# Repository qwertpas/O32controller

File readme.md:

Small robots often use servos or small brushed DC motors, but they are not as power dense as the brushless DC (BLDC) motors commonly found in drones. Called the Ø32 because the M2 mounting holes are on a 32mm diameter circle, this project controls 7-15V motors with accurate position feedback and field-oriented control (FOC), while fitting almost completely behind a 2304 or larger drone motor.

Specs:
- 27mm x 27mm x 0.8mm, 4-layer, 1oz copper PCB
- M2 mounting holes on a 32mm diameter circle
- 7-15V input, bus voltage sensing
- MCU internal temperature sensor and external NTC reading
- built-in high speed 12-bit magnetic angle sensor and external SPI encoder port (3.3V)
- 3 shunt current sensing and overcurrent protection 
- 2x 2-pin JST-SH connectors for RS-485 communication, allowing daisy chaining
- 1x 4-pin JST-SH connector for SWD programming/debug and UART_TX output
- FOC capable

Critical components:
- STSPIN32F0A BLDC gate driver and Cortex-M0 MCU
- MA702 magnetic angle sensor
- CSD88584Q5DC half-bridge (50A continuous)

[Full schematic PDF](https://github.com/qwertpas/O32controller/blob/master/v3/output_v3.1/O32controller.pdf)

More info on Hackaday.io: https://hackaday.io/project/189115-32-bldc-controller

Firmware here: https://github.com/qwertpas/O32controller_FW

Changelog from v3 to v3.1:
- Larger 15V TVS diode D2 (SMF15A) because there is space 
- Changed R4 from 121kΩ to 33kΩ for a more reasonable phase current limit of 43A using the 100mV comparator 
- Replaced external SPI pads with UART and GPIO PA15 pads for direct communication with another microcontroller without need for RS485 transceiver 
- Replace MA702 (12-bit magnetic encoder) with MA732 (14-bit, adjustable filter)
- Picked out parts in stock from LCSC as much as possible

Changelog from v2 to v3:
- Fixed TVS diode direction on VBUS (!!)
- Changed to 37x 22uF ceramic capacitors instead of 2x 100uF electrolytic capacitors for a thinner PCBA
- Removed I2C (formerly on PB6 and PB7)
- Moved UART_TX and UART_RX to PB6 and PB7 (formerly on PA2 and PA15)
- Changed PA2 to ADC1 CH2 to read a 10k NTC, soldered to pads
- Changed PA15 to GPIO for external SPI CS (MAG2_CS)
- Added 13.7k pulldown on SPI_MISO to keep it determined when no devices selected
- Changed to 100nF filter capacitor on BUS_SENSE instead of 1nF to charge ADC capacitor better and for smoother data
- Changed BUS_SENSE gain to 5x instead of 5.12x to reuse 13.7k resistor
- Removed test point on BUS_SENSE
- Added test point on LED_STATUS (for debugging using GPIO)
- Removed NRST pushbutton to create space
- Added 6 pads with 0.5mm pitch to solder FFC cable for an external SPI encoder
- Changed vias to 0.25mm hole size and 0.55mm plated diameter instead of 0.2/0.5 for easier manufacturability
- Changed minimum track clearance from 0.2mm to 0.16mm to make space for larger vias
- Changed to equal number of vias (27) on the top side of all three shunt resistors
- Changed most silkscreen text to 0.8mm width/height
- Put all footprints and 3D models in project library O32controller

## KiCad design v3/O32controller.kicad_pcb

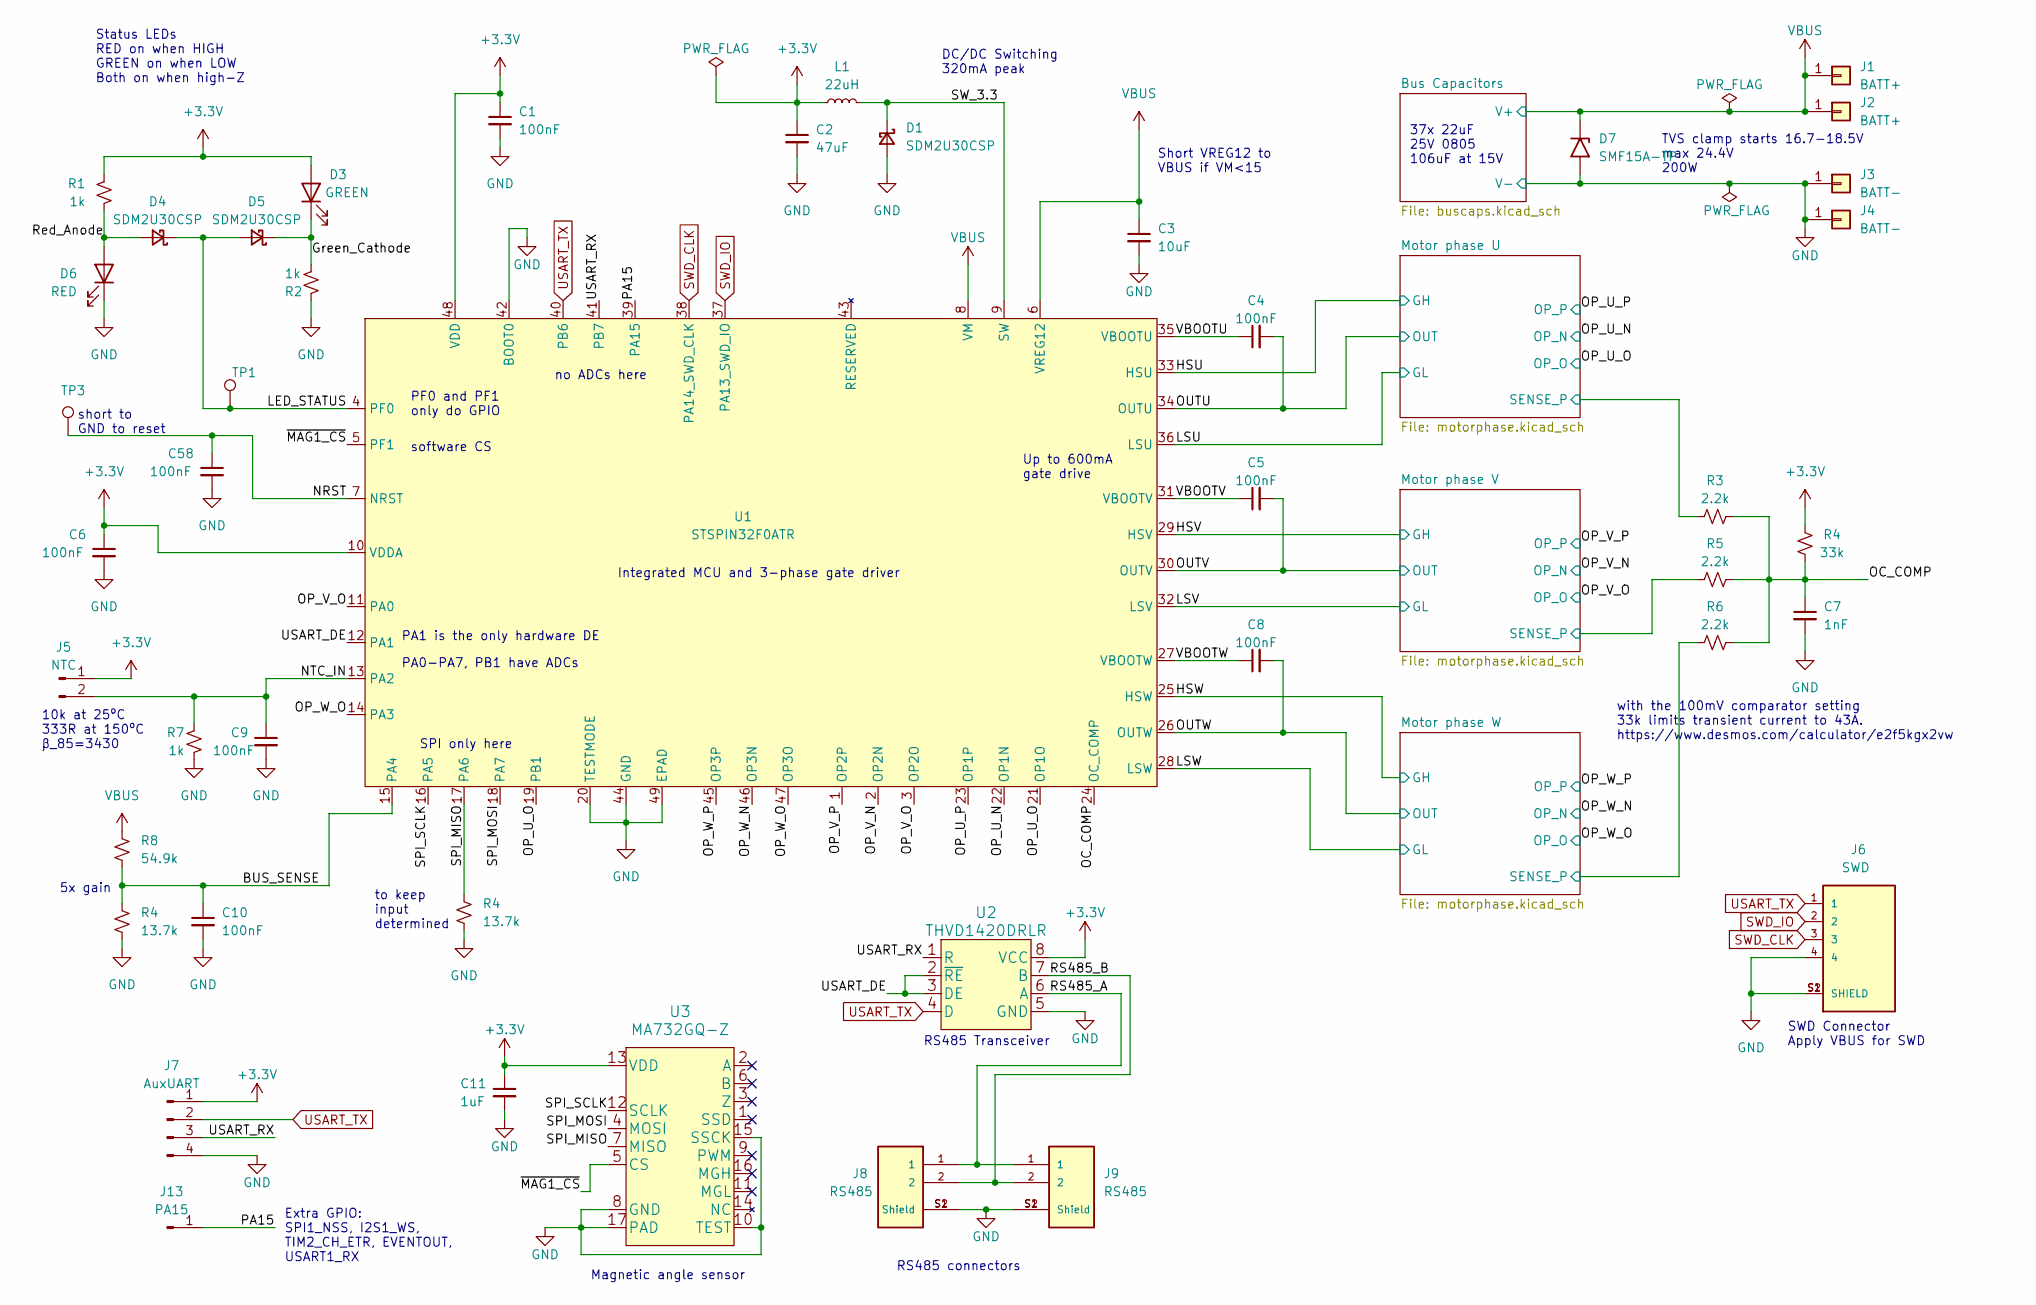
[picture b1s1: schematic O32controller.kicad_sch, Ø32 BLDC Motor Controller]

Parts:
C1, C4, C5, C6, C8, C9, C10, C58: 100nF; C_0402_1005Metric; MPN CL05B104KB54PNC; LCSC C307331
C2: 47uF; C_0603_1608Metric; MPN GRM188R60J476ME15D; LCSC C140782
C3: 10uF; C_0603_1608Metric; MPN GRM188R6YA106MA73D; LCSC C194427
C7: 1nF; C_0402_1005Metric; MPN 0402B102K500NT; LCSC C1523
C11: 1uF; C_0402_1005Metric; MPN CL05A105KA5NQNC; LCSC C52923
D1, D4, D5: SDM2U30CSP; SDM2U30CSP-7; MPN SDM2U30CSP-7
D3: GREEN; LED_0603_1608Metric; MPN LTST-C191KGKT; LCSC C125098
D6: RED; LED_0603_1608Metric; MPN KT-0603R; LCSC C2286
D7: SMF15A-TP; D_SMF; MPN SMF15A-TP; LCSC C914420
J1, J2: BATT+; SolderWire-Actual_1x01_D1.7mm_OD_2.75mm
J3, J4: BATT-; SolderWire-Actual_1x01_D1.7mm_OD_2.75mm
J5: NTC; SolderNTC-1.27mm
J6: SWD; JST_SM04B-SRSS-TB(LF)(SN); MPN SM04B-SRSS-TB(LF)(SN)
J7: AuxUART; SolderUART-1.27mm
J8, J9: RS485; JST_SM02B-SRSS-TB(LF)(SN); MPN SM02B-SRSS-TB_LF__SN_; LCSC C160402
J13: PA15; SolderPad1-1.27mm
L1: 22uH; IND_VLS201612CX-220M-1; MPN VLS201612CX-220M-1; LCSC C2044426
R1, R2, R7: 1k; R_0402_1005Metric; MPN 0402WGF1001TCE; LCSC C11702
R3, R5, R6: 2.2k; R_0402_1005Metric; MPN 0402WGF2201TCE; LCSC C25879
R4: 33k; R_0402_1005Metric; MPN 0402WGF3302TCE; LCSC C25779
R8: 54.9k; R_0402_1005Metric; MPN RC0402FR-0754K9L; LCSC C137959
TP1, TP3: TestPoint; TestPoint_Pad_Rect
U1: STSPIN32F0ATR; VFQFPN-48-1EP_7x7mm_P0.5mm_EP2.8x2.8mm; MPN STSPIN32F0ATR; LCSC C2651733
U2: THVD1420DRLR; THVD1420DRLR_SOT-585; MPN THVD1420DRLR
U3: MA732GQ-Z; QFN-16_MA732; MPN MA732GQ-Z

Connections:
/Green_Cathode: D3.1 (K), D5.1 (K), R2.1
/HSU: U1.33 (HSU); also elsewhere on the board
/HSV: U1.29 (HSV); also elsewhere on the board
/HSW: U1.25 (HSW); also elsewhere on the board
/LED_STATUS: D4.1 (K), D5.2 (A), TP1.1, U1.4 (PF0)
/LSU: U1.36 (LSU); also elsewhere on the board
/LSV: U1.32 (LSV); also elsewhere on the board
/LSW: U1.28 (LSW); also elsewhere on the board
/Motor phase U/SENSE_P: R3.2; also elsewhere on the board
/Motor phase V/SENSE_P: R5.2; also elsewhere on the board
/Motor phase W/SENSE_P: R6.2; also elsewhere on the board
/NRST: C58.1, TP3.1, U1.7 (NRST)
/NTC_IN: C9.1, J5.2, R7.2, U1.13 (PA2)
/OP_U_N: U1.22 (OP1N); also elsewhere on the board
/OP_U_O: U1.19 (PB1), U1.21 (OP1O); also elsewhere on the board
/OP_U_P: U1.23 (OP1P); also elsewhere on the board
/OP_V_N: U1.2 (OP2N); also elsewhere on the board
/OP_V_O: U1.3 (OP2O), U1.11 (PA0); also elsewhere on the board
/OP_V_P: U1.1 (OP2P); also elsewhere on the board
/OP_W_N: U1.46 (OP3N); also elsewhere on the board
/OP_W_O: U1.14 (PA3), U1.47 (OP3O); also elsewhere on the board
/OP_W_P: U1.45 (OP3P); also elsewhere on the board
/OUTU: C4.2, U1.34 (OUTU); also elsewhere on the board
/OUTV: C5.2, U1.30 (OUTV); also elsewhere on the board
/OUTW: C8.2, U1.26 (OUTW); also elsewhere on the board
/PA15: J13.1, U1.39 (PA15)
/RS485_A: J8.1, J9.1, U2.6 (A)
/RS485_B: J8.2, J9.2, U2.7 (B)
/Red_Anode: D4.2 (A), D6.2 (A), R1.1
/SPI_MOSI: U1.18 (PA7), U3.4 (MOSI)
/SPI_SCLK: U1.16 (PA5), U3.12 (SCLK)
/SW_3.3: D1.1 (K), L1.2, U1.9 (SW)
/USART_DE: U1.12 (PA1), U2.2 (~RE), U2.3 (DE)
/USART_RX: J7.3, U1.41 (PB7), U2.1 (R)
/VBOOTU: C4.1, U1.35 (VBOOTU)
/VBOOTV: C5.1, U1.31 (VBOOTV)
/VBOOTW: C8.1, U1.27 (VBOOTW)
/~MAG1_CS: U1.5 (PF1), U3.5 (CS)
SWD_CLK: J6.3, U1.38 (PA14_SWD_CLK)
SWD_IO: J6.2, U1.37 (PA13_SWD_IO)
USART_TX: J6.1, J7.2, U1.40 (PB6), U2.4 (D)
VBUS: C3.1, D7.1 (A1), J1.1, J2.1, R8.1, U1.6 (VREG12), U1.8 (VM); also elsewhere on the board

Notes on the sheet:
PA1 is the only hardware DE
to keep input determined
RS485 Transceiver
short to GND to reset
Short VREG12 to VBUS if VM<15
Up to 600mA gate drive
Extra GPIO: SPI1_NSS, I2S1_WS, TIM2_CH_ETR, EVENTOUT, USART1_RX
37x 22uF 25V 0805 106uF at 15V
DC/DC Switching 320mA peak
Integrated MCU and 3-phase gate driver
PF0 and PF1 only do GPIO
PA0-PA7, PB1 have ADCs
TVS clamp starts 16.7-18.5V max 24.4V 200W
10k at 25ºC 333R at 150ºC β_85=3430
with the 100mV comparator setting 33k limits transient current to 43A. https://www.desmos.com/calculator/e2f5kgx2vw
5x gain
no ADCs here
SPI only here
Magnetic angle sensor
RS485 connectors
software CS
SWD Connector Apply VBUS for SWD
Status LEDs RED on when HIGH GREEN on when LOW Both on when high-Z

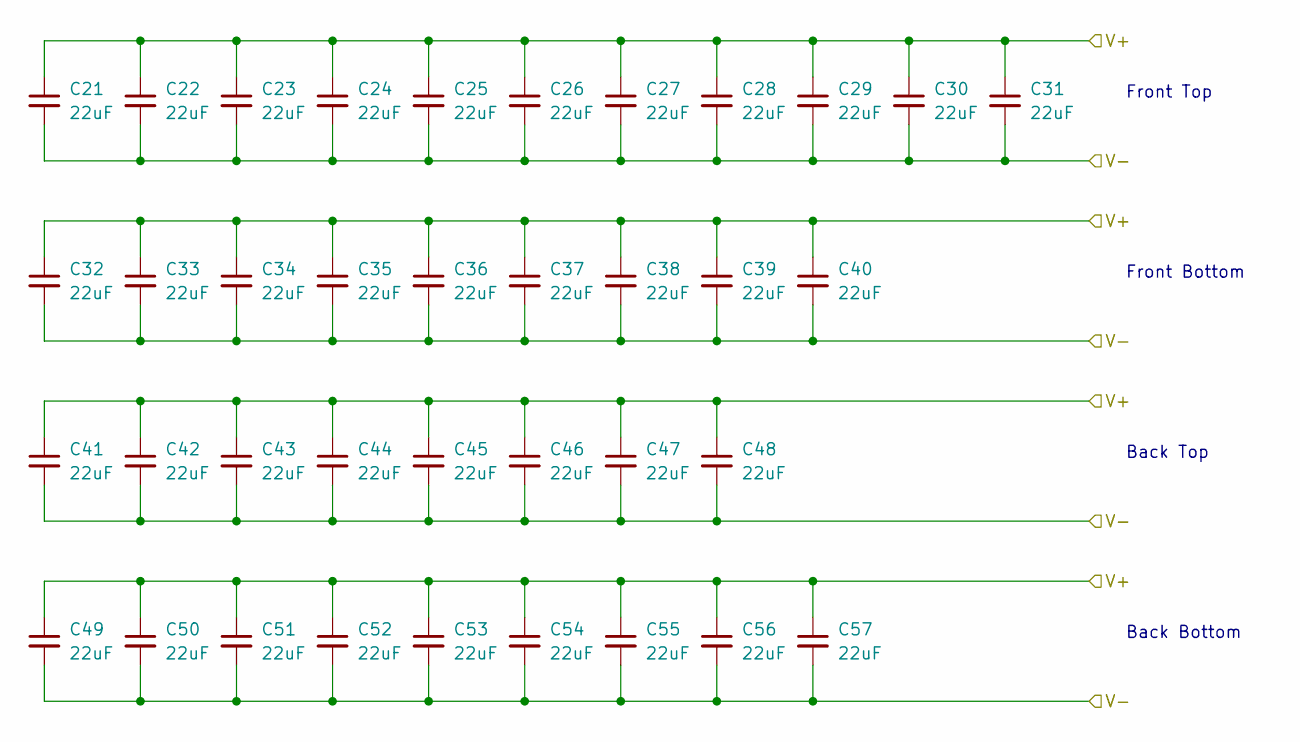
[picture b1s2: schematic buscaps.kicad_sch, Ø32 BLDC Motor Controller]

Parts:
C21, C22, C23, C24, C25, C26, C27, C28, C29, C30, C31, C32, C33, C34, C35, C36, C37, C38, C39, C40, C41, C42, C43, C44, C45, C46, C47, C48, C49, C50, C51, C52, C53, C54, C55, C56, C57: 22uF; C_0805_nosilk; MPN CL21A226MAQNNNE; LCSC C45783

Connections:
VBUS: C21.1, C22.1, C23.1, C24.1, C25.1, C26.1, C27.1, C28.1, C29.1, C30.1, C31.1, C32.1, C33.1, C34.1, C35.1, C36.1, C37.1, C38.1, C39.1, C40.1, C41.1, C42.1, C43.1, C44.1, C45.1, C46.1, C47.1, C48.1, C49.1, C50.1, C51.1, C52.1, C53.1, C54.1, C55.1, C56.1, C57.1; also elsewhere on the board

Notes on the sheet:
Back Bottom
Back Top
Front Top
Front Bottom

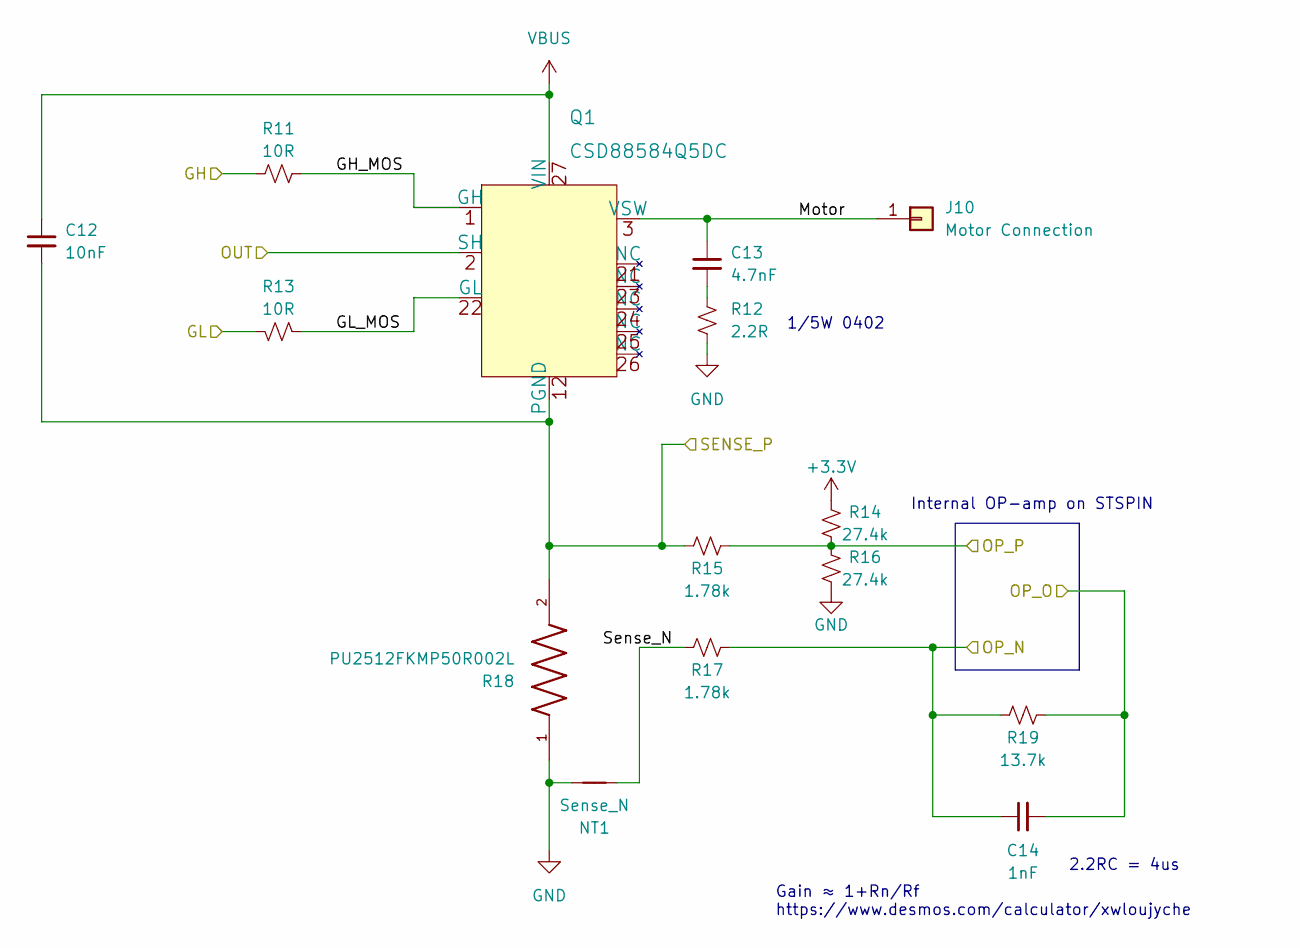
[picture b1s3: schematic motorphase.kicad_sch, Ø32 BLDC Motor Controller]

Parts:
C12: 10nF; C_0402_1005Metric; MPN CL05B103KB5NNNC; LCSC C15195
C13: 4.7nF; C_0402_1005Metric; MPN 0402B472K500NT; LCSC C1538
C14: 1nF; C_0402_1005Metric; MPN 0402B102K500NT; LCSC C1523
J10: Motor Connection; SolderWire-Actual_1x01_D1.7mm_OD_2.75mm
NT1: Sense_N; NetTie-2_SMD_Pad0.25mm
Q1: CSD88584Q5DC; CSD88584Q5DCT; MPN CSD88584Q5DC
R11, R13: 10R; R_0402_1005Metric; MPN SR0402FR-7T10RL; LCSC C854481
R12: 2.2R; R_0402_1005Metric; MPN RK73B1ETTP2R2J; LCSC C131536
R14, R16: 27.4k; R_0402_1005Metric; MPN RC0402FR-0727K4L; LCSC C273730
R15, R17: 1.78k; R_0402_1005Metric; MPN ARG02FTC1781; LCSC C284379
R18: PU2512FKMP50R002L; R_Shunt_2512_6332Metric; MPN PU2512FKMP50R002L; LCSC C2090861
R19: 13.7k; R_0402_1005Metric; MPN RC0402FR-0713K7L; LCSC C274888

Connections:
/HSU: R11.1; also elsewhere on the board
/LSU: R13.2; also elsewhere on the board
/Motor phase U/GH_MOS: Q1.1 (GH), R11.2
/Motor phase U/GL_MOS: Q1.22 (GL), R13.1
/Motor phase U/Motor: C13.1, J10.1, Q1.3 (VSW)
/Motor phase U/SENSE_P: C12.2, Q1.12 (PGND), R15.1, R18.2; also elsewhere on the board
/Motor phase U/Sense_N: NT1.1, R17.1
/OP_U_N: C14.1, R17.2, R19.1; also elsewhere on the board
/OP_U_O: C14.2, R19.2; also elsewhere on the board
/OP_U_P: R14.1, R15.2, R16.2; also elsewhere on the board
/OUTU: Q1.2 (SH); also elsewhere on the board
unnamed: C13.2, R12.1
VBUS: C12.1, Q1.27 (VIN); also elsewhere on the board

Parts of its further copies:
C15, C18: 10nF; C_0402_1005Metric; MPN CL05B103KB5NNNC; LCSC C15195
C16, C19: 4.7nF; C_0402_1005Metric; MPN 0402B472K500NT; LCSC C1538
C17, C20: 1nF; C_0402_1005Metric; MPN 0402B102K500NT; LCSC C1523
J11, J12: Motor Connection; SolderWire-Actual_1x01_D1.7mm_OD_2.75mm
NT2, NT3: Sense_N; NetTie-2_SMD_Pad0.25mm
Q2, Q3: CSD88584Q5DC; CSD88584Q5DCT; MPN CSD88584Q5DC
R20, R22, R29, R31: 10R; R_0402_1005Metric; MPN SR0402FR-7T10RL; LCSC C854481
R21, R30: 2.2R; R_0402_1005Metric; MPN RK73B1ETTP2R2J; LCSC C131536
R23, R25, R32, R34: 27.4k; R_0402_1005Metric; MPN RC0402FR-0727K4L; LCSC C273730
R24, R26, R33, R35: 1.78k; R_0402_1005Metric; MPN ARG02FTC1781; LCSC C284379
R27, R36: PU2512FKMP50R002L; R_Shunt_2512_6332Metric; MPN PU2512FKMP50R002L; LCSC C2090861
R28, R37: 13.7k; R_0402_1005Metric; MPN RC0402FR-0713K7L; LCSC C274888

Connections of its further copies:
/HSV: R20.1; also elsewhere on the board
/HSW: R29.1; also elsewhere on the board
/LSV: R22.2; also elsewhere on the board
/LSW: R31.2; also elsewhere on the board
/Motor phase V/GH_MOS: Q2.1 (GH), R20.2
/Motor phase V/GL_MOS: Q2.22 (GL), R22.1
/Motor phase V/Motor: C16.1, J11.1, Q2.3 (VSW)
/Motor phase V/SENSE_P: C15.2, Q2.12 (PGND), R24.1, R27.2; also elsewhere on the board
/Motor phase V/Sense_N: NT2.1, R26.1
/Motor phase W/GH_MOS: Q3.1 (GH), R29.2
/Motor phase W/GL_MOS: Q3.22 (GL), R31.1
/Motor phase W/Motor: C19.1, J12.1, Q3.3 (VSW)
/Motor phase W/SENSE_P: C18.2, Q3.12 (PGND), R33.1, R36.2; also elsewhere on the board
/Motor phase W/Sense_N: NT3.1, R35.1
/OP_V_N: C17.1, R26.2, R28.1; also elsewhere on the board
/OP_V_O: C17.2, R28.2; also elsewhere on the board
/OP_V_P: R23.1, R24.2, R25.2; also elsewhere on the board
/OP_W_N: C20.1, R35.2, R37.1; also elsewhere on the board
/OP_W_O: C20.2, R37.2; also elsewhere on the board
/OP_W_P: R32.1, R33.2, R34.2; also elsewhere on the board
/OUTV: Q2.2 (SH); also elsewhere on the board
/OUTW: Q3.2 (SH); also elsewhere on the board
unnamed: C16.2, R21.1
unnamed: C19.2, R30.1
VBUS: C15.1, C18.1, Q2.27 (VIN), Q3.27 (VIN); also elsewhere on the board

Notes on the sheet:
Internal OP-amp on STSPIN
2.2RC = 4us
Gain ≈ 1+Rn/Rf https://www.desmos.com/calculator/xwloujyche
1/5W 0402

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
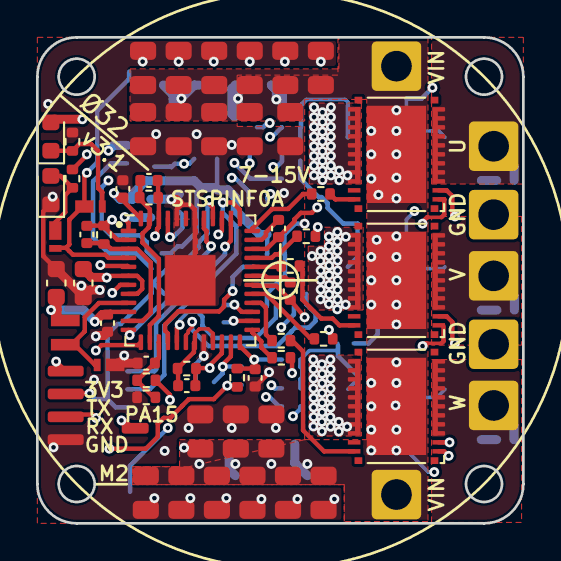
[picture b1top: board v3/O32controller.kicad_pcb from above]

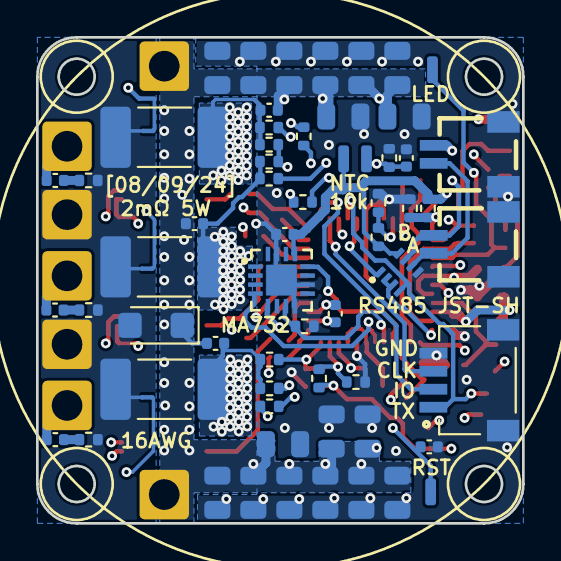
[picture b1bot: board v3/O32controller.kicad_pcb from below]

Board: 4 copper layers, 27.0 x 27.0 mm, 126 parts (62 on the bottom side), 62 nets.

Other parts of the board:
R9, R10: 13.7k; R_0402_1005Metric

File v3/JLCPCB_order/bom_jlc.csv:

Comment,Designator,Footprint,LCSC
"100nF","C1,C4,C5,C6,C8,C9,C10,C58","Capacitor_SMD:C_0402_1005Metric","C100072"
"1uF","C11","Capacitor_SMD:C_0402_1005Metric","C126521"
"10nF","C12,C15,C18","Capacitor_SMD:C_0402_1005Metric","C15195"
"4.7nF","C13,C16,C19","Capacitor_SMD:C_0402_1005Metric","C415704"
"47uF","C2","Capacitor_SMD:C_0603_1608Metric","C140782"
"22uF","C21,C22,C23,C24,C25,C26,C27,C28,C29,C30,C31,C32,C33,C34,C35,C36,C37,C38,C39,C40,C41,C42,C43,C44,C45,C46,C47,C48,C49,C50,C51,C52,C53,C54,C55,C56,C57","O32controller:C_0805_nosilk","C45783"
"10uF","C3","Capacitor_SMD:C_0603_1608Metric","C194427"
"1nF","C7,C14,C17,C20","Capacitor_SMD:C_0402_1005Metric","C527029"
"SDM2U30CSP","D1,D4,D5","O32controller:SDM2U30CSP-7","C3001723"
"ESDA17P20-1F2","D2","O32controller:SMT2_0P91X0P63_STM-L","C3713569"
"GREEN","D3","LED_SMD:LED_0603_1608Metric","C125098"
"RED","D6","LED_SMD:LED_0603_1608Metric","C125099"
"SWD","J6","O32controller:JST_SM04B-SRSS-TB(LF)(SN)","C160404"
"RS485","J8,J9","O32controller:JST_SM02B-SRSS-TB(LF)(SN)","C160402"
"22uH","L1","O32controller:IND_VLS201612CX-220M-1","C2044426"
"CSD88584Q5DC","Q1,Q2,Q3","O32controller:CSD88584Q5DCT",""
"1k","R1,R2,R7","Resistor_SMD:R_0402_1005Metric","C106235"
"10R","R11,R13,R20,R22,R29,R31","Resistor_SMD:R_0402_1005Metric","C854481"
"2.2R","R12,R21,R30","Resistor_SMD:R_0402_1005Metric","C2079158"
"27.4k","R14,R16,R23,R25,R32,R34","Resistor_SMD:R_0402_1005Metric","C273730"
"1.78k","R15,R17,R24,R26,R33,R35","Resistor_SMD:R_0402_1005Metric","C185450"
"PU2512FKMP50R002L","R18,R27,R36","O32controller:R_Shunt_2512_6332Metric","C2090861"
"2.2k","R3,R5,R6","Resistor_SMD:R_0402_1005Metric","C114762"
"121k","R4","Resistor_SMD:R_0402_1005Metric","C4153138"
"54.9k","R8","Resistor_SMD:R_0402_1005Metric","C137959"
"13.7k","R9,R10,R19,R28,R37","Resistor_SMD:R_0402_1005Metric","C274888"
"STSPIN32F0ATR","U1","O32controller:VFQFPN-48-1EP_7x7mm_P0.5mm_EP2.8x2.8mm","C2651733"
"THVD1420DRLR","U2","O32controller:THVD1420DRLR_SOT-585",""
"MA702GQ-P","U3","O32controller:MA702GQ-P",""

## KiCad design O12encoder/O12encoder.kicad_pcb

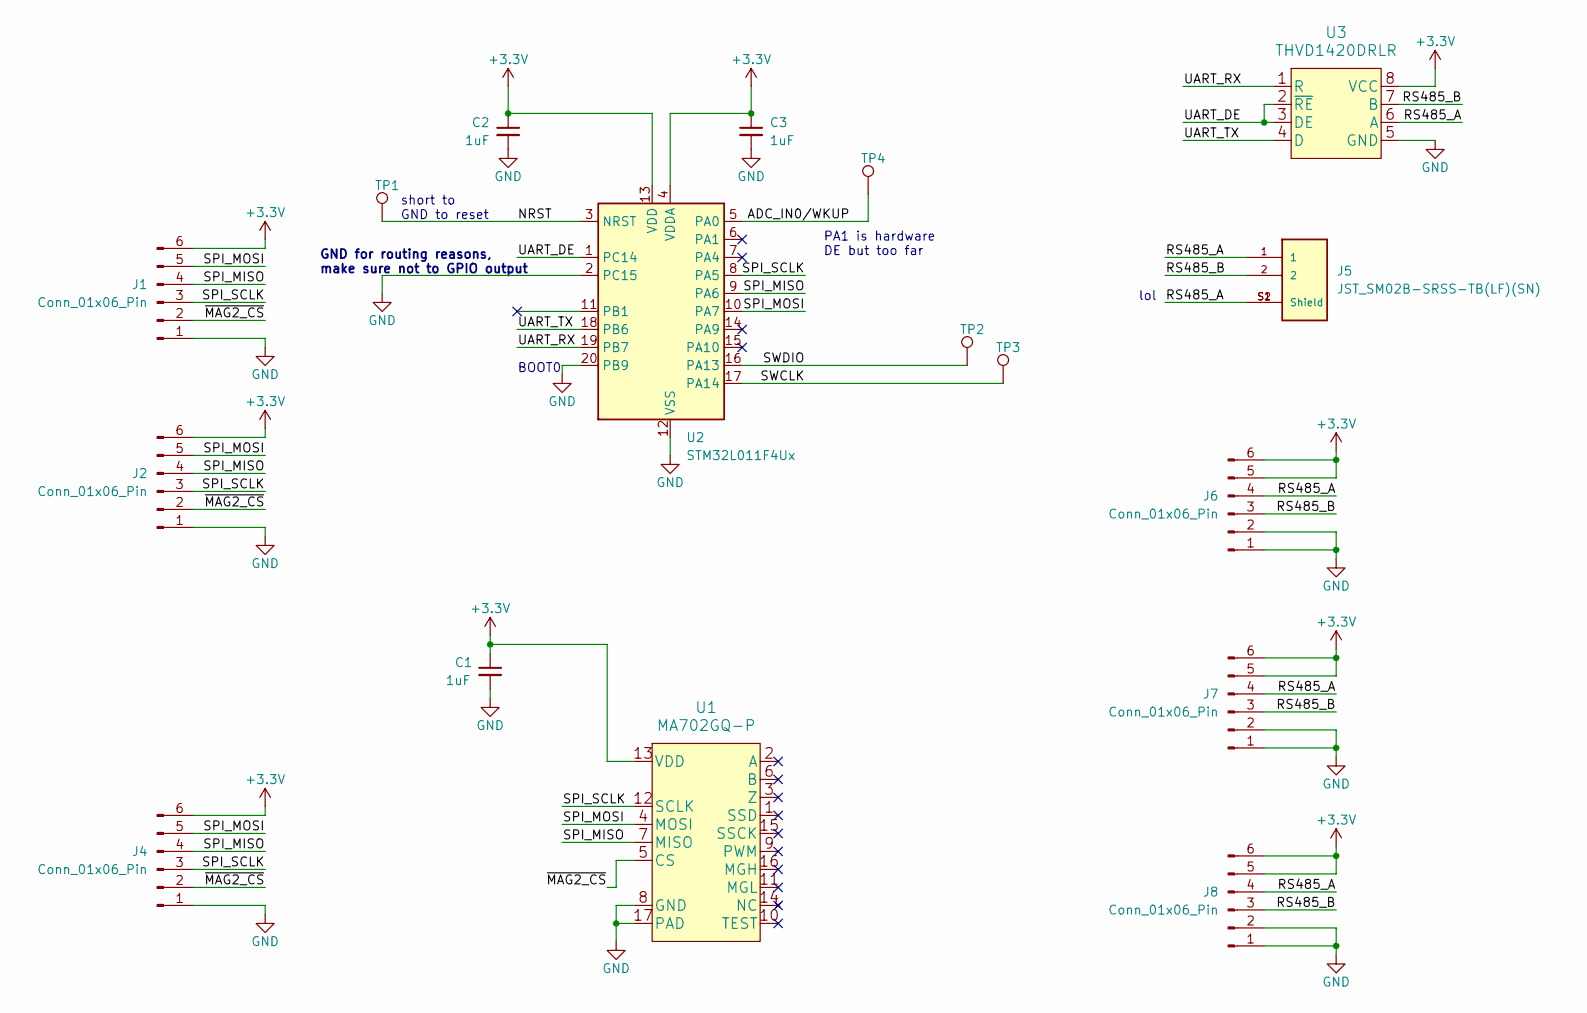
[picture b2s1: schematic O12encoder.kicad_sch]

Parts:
C1: 1uF; C_0402_1005Metric; MPN GCM155C71A105KE38D
C2, C3: 1uF; C_0402_1005Metric
J1, J2, J4, J6, J7, J8: Conn_01x06_Pin; FFC_0.5mm_6p
J5: JST_SM02B-SRSS-TB(LF)(SN)
TP1, TP2, TP3, TP4: TestPoint; TestPoint_Pad_Rect
U1: MA702GQ-P
U2: STM32L011F4Ux; ST_UFQFPN-20_3x3mm_P0.5mm; MPN STM32L011F4U3TR
U3: THVD1420DRLR; THVD1420DRLR_SOT-585; MPN THVD1420DRLR

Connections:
+3.3V: C1.1, C2.1, C3.1, J1.6, J2.6, J4.6, J6.5, J6.6, J7.5, J7.6, J8.5, J8.6, U1.13 (VDD), U2.4 (VDDA), U2.13 (VDD), U3.8 (VCC)
/ADC_IN0/WKUP: TP4.1, U2.5 (PA0)
/NRST: TP1.1, U2.3 (NRST)
/RS485_A: J5.1, J5.S1 (Shield), J5.S2 (Shield), J6.4, J7.4, J8.4, U3.6 (A)
/RS485_B: J5.2, J6.3, J7.3, J8.3, U3.7 (B)
/SPI_MISO: J1.4, J2.4, J4.4, U1.7 (MISO), U2.9 (PA6)
/SPI_MOSI: J1.5, J2.5, J4.5, U1.4 (MOSI), U2.10 (PA7)
/SPI_SCLK: J1.3, J2.3, J4.3, U1.12 (SCLK), U2.8 (PA5)
/SWCLK: TP3.1, U2.17 (PA14)
/SWDIO: TP2.1, U2.16 (PA13)
/UART_DE: U2.1 (PC14), U3.2 (~RE), U3.3 (DE)
/UART_RX: U2.19 (PB7), U3.1 (R)
/UART_TX: U2.18 (PB6), U3.4 (D)
/~MAG2_CS: J1.2, J2.2, J4.2, U1.5 (CS)
GND: C1.2, C2.2, C3.2, J1.1, J2.1, J4.1, J6.1, J6.2, J7.1, J7.2, J8.1, J8.2, U1.8 (GND), U1.17 (PAD), U2.2 (PC15), U2.12 (VSS), U2.20 (PB9), U3.5 (GND)

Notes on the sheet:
GND for routing reasons, make sure not to GPIO output
BOOT0
PA1 is hardware DE but too far
short to GND to reset
lol

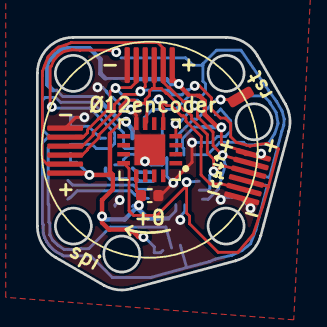
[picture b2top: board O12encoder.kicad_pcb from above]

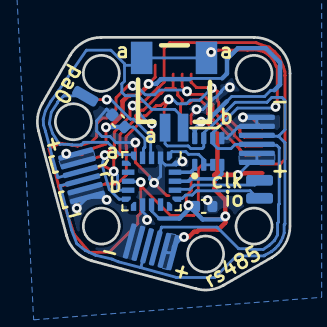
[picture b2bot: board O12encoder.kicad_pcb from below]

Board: 2 copper layers, 14.0 x 14.0 mm, 17 parts (11 on the bottom side), 15 nets.

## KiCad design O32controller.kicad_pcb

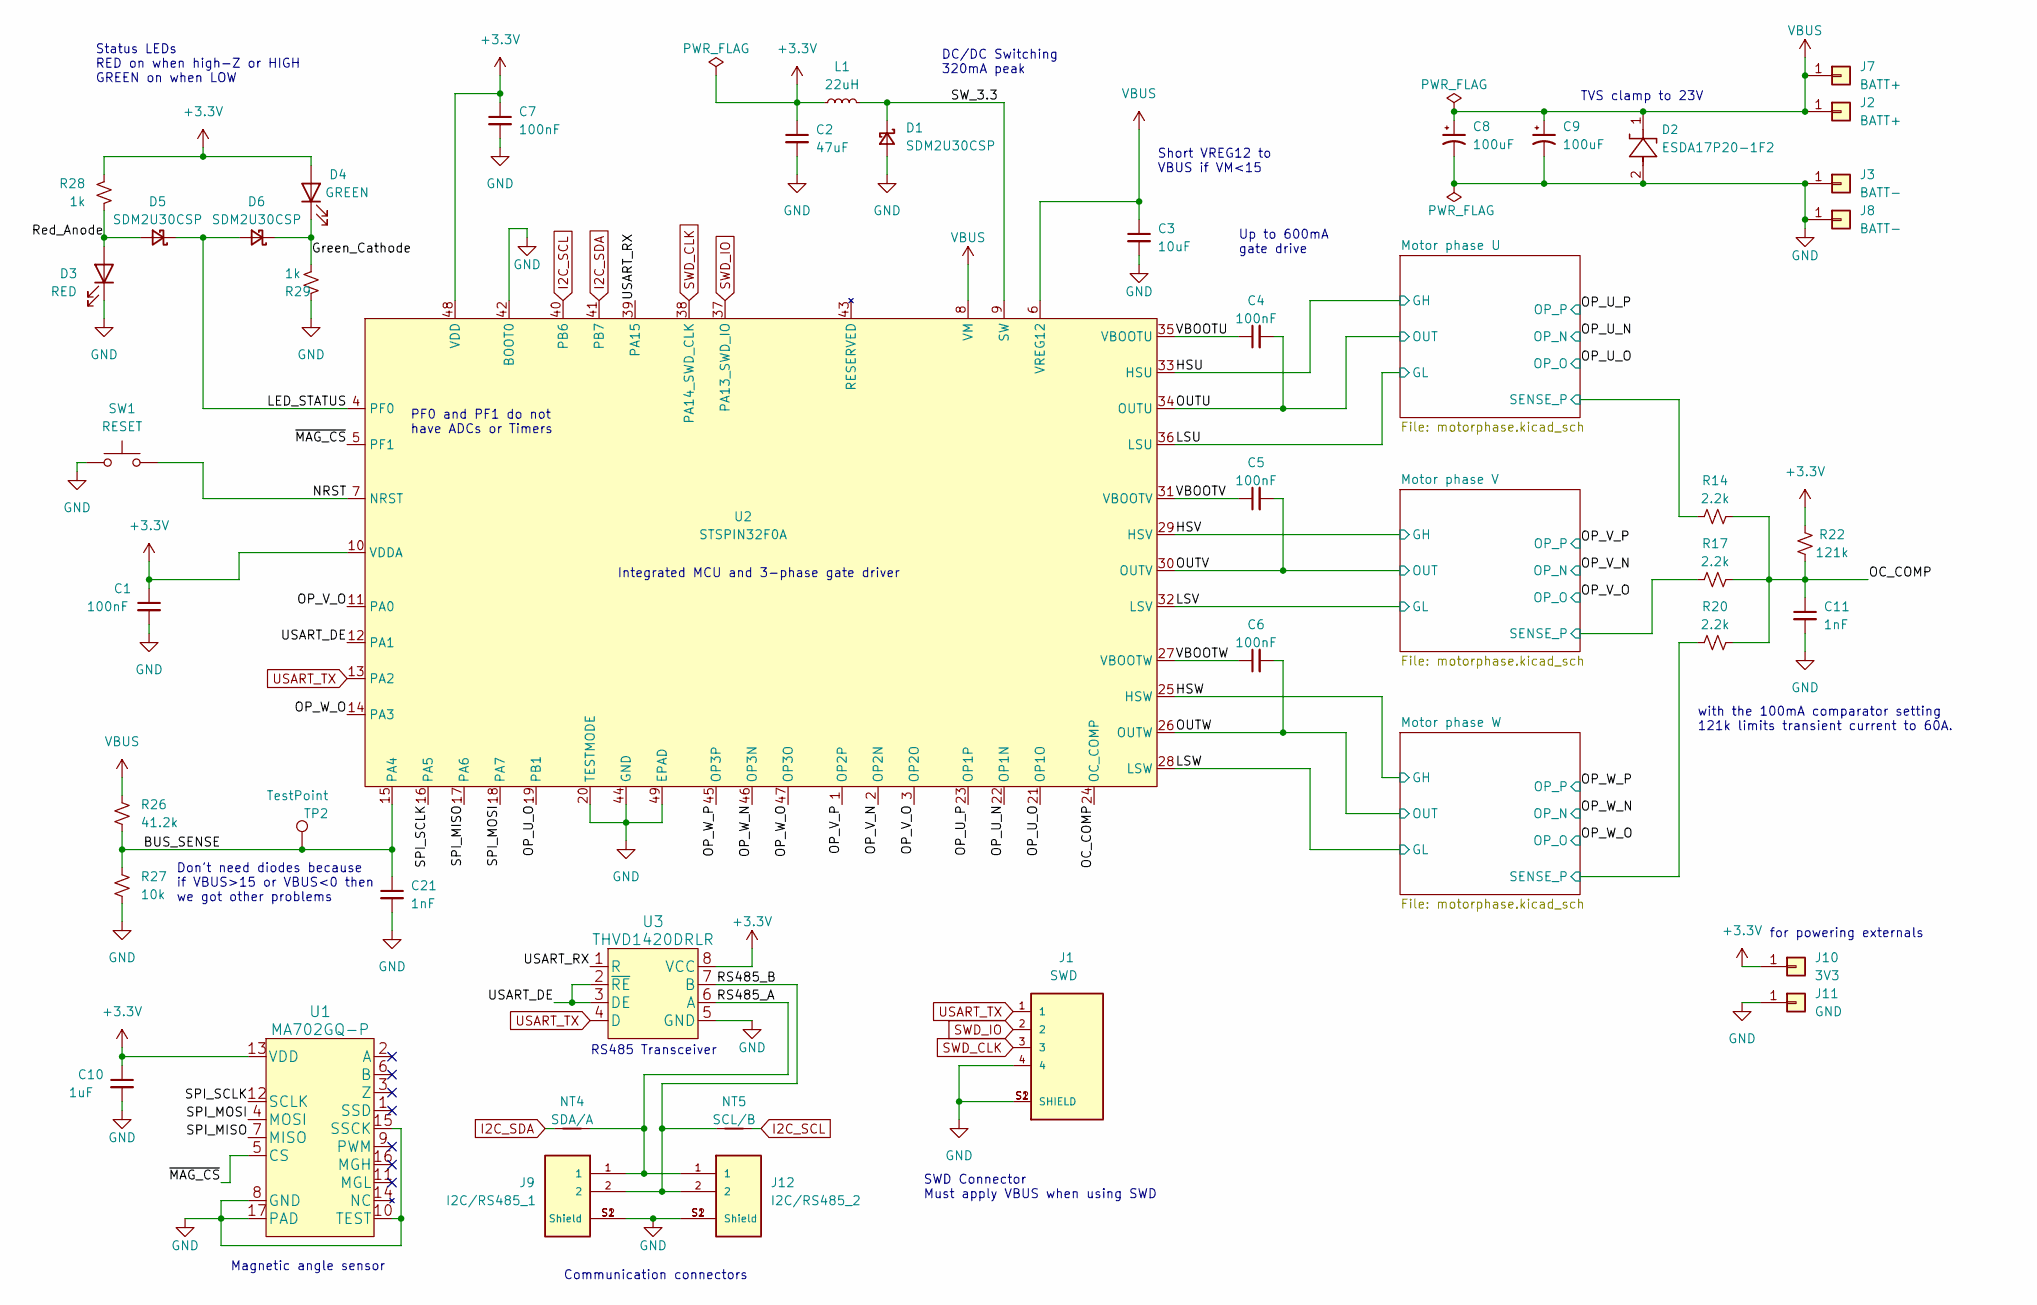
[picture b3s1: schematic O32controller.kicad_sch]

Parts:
C1, C4, C5, C6, C7: 100nF; C_0402_1005Metric
C2: 47uF; C_0603_1608Metric
C3: 10uF; C_0603_1608Metric
C8, C9: 100uF; CAP_EEEFN1E101UP
C10: 1uF; C_0402_1005Metric
C11, C21: 1nF; C_0402_1005Metric
D1, D5, D6: SDM2U30CSP; SDM2U30CSP-7
D2: ESDA17P20-1F2; SMT2_0P91X0P63_STM-L
D3: RED; LED_0603_1608Metric
D4: GREEN; LED_0603_1608Metric
J1: SWD; JST_SM04B-SRSS-TB(LF)(SN)
J2, J7: BATT+; SolderWire-Actual_1x01_D1.7mm_OD_2.75mm
J3, J8: BATT-; SolderWire-Actual_1x01_D1.7mm_OD_2.75mm
J9: I2C/RS485_1; JST_SM02B-SRSS-TB(LF)(SN)
J10: 3V3; SolderWire-Actual_1x01_D1.25mm_OD_1.8mm
J11: GND; SolderWire-Actual_1x01_D1.25mm_OD_1.8mm
J12: I2C/RS485_2; JST_SM02B-SRSS-TB(LF)(SN)
L1: 22uH; IND_VLS201612CX-220M-1
NT4: SDA/A; NetTie-2_SMD_Pad0.25mm
NT5: SCL/B; NetTie-2_SMD_Pad0.25mm
R14, R17, R20: 2.2k; R_0402_1005Metric
R22: 121k; R_0402_1005Metric
R26: 41.2k; R_0402_1005Metric
R27: 10k; R_0402_1005Metric
R28, R29: 1k; R_0402_1005Metric
SW1: RESET; Tactile_Switch_EVQ-P7A01P
TP2: TestPoint; TestPoint_Pad_D1.0mm
U1: MA702GQ-P
U2: STSPIN32F0A; VFQFPN-48-1EP_7x7mm_P0.5mm_EP2.8x2.8mm
U3: THVD1420DRLR; THVD1420DRLR_SOT-585

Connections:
+3.3V: C1.1, C2.1, C7.1, C10.1, D4.2 (A), J10.1, L1.1, R22.1, R28.2, U1.13 (VDD), U2.10 (VDDA), U2.48 (VDD), U3.8 (VCC); also elsewhere on the board
/BUS_SENSE: C21.1, R26.2, R27.1, TP2.1, U2.15 (PA4)
/Green_Cathode: D4.1 (K), D6.1 (K), R29.1
/HSU: U2.33 (HSU); also elsewhere on the board
/HSV: U2.29 (HSV); also elsewhere on the board
/HSW: U2.25 (HSW); also elsewhere on the board
/LED_STATUS: D5.1 (K), D6.2 (A), U2.4 (PF0)
/LSU: U2.36 (LSU); also elsewhere on the board
/LSV: U2.32 (LSV); also elsewhere on the board
/LSW: U2.28 (LSW); also elsewhere on the board
/Motor phase U/SENSE_P: R14.2; also elsewhere on the board
/Motor phase V/SENSE_P: R17.2; also elsewhere on the board
/Motor phase W/SENSE_P: R20.2; also elsewhere on the board
/NRST: SW1.2, U2.7 (NRST)
/OC_COMP: C11.1, R14.1, R17.1, R20.1, R22.2, U2.24 (OC_COMP)
/OP_U_N: U2.22 (OP1N); also elsewhere on the board
/OP_U_O: U2.19 (PB1), U2.21 (OP1O); also elsewhere on the board
/OP_U_P: U2.23 (OP1P); also elsewhere on the board
/OP_V_N: U2.2 (OP2N); also elsewhere on the board
/OP_V_O: U2.3 (OP2O), U2.11 (PA0); also elsewhere on the board
/OP_V_P: U2.1 (OP2P); also elsewhere on the board
/OP_W_N: U2.46 (OP3N); also elsewhere on the board
/OP_W_O: U2.14 (PA3), U2.47 (OP3O); also elsewhere on the board
/OP_W_P: U2.45 (OP3P); also elsewhere on the board
/OUTU: C4.2, U2.34 (OUTU); also elsewhere on the board
/OUTV: C5.2, U2.30 (OUTV); also elsewhere on the board
/OUTW: C6.2, U2.26 (OUTW); also elsewhere on the board
/RS485_A: J9.1, J12.1, NT4.2, U3.6 (A)
/RS485_B: J9.2, J12.2, NT5.2, U3.7 (B)
/Red_Anode: D3.2 (A), D5.2 (A), R28.1
/SPI_MISO: U1.7 (MISO), U2.17 (PA6)
/SPI_MOSI: U1.4 (MOSI), U2.18 (PA7)
/SPI_SCLK: U1.12 (SCLK), U2.16 (PA5)
/SW_3.3: D1.1 (K), L1.2, U2.9 (SW)
/USART_DE: U2.12 (PA1), U3.2 (~RE), U3.3 (DE)
/USART_RX: U2.39 (PA15), U3.1 (R)
/VBOOTU: C4.1, U2.35 (VBOOTU)
/VBOOTV: C5.1, U2.31 (VBOOTV)
/VBOOTW: C6.1, U2.27 (VBOOTW)
/~MAG_CS: U1.5 (CS), U2.5 (PF1)
GND: C1.2, C2.2, C3.2, C7.2, C8.2, C9.2, C10.2, C11.2, C21.2, D1.2 (A), D2.2, D3.1 (K), J1.4, J1.S1 (SHIELD), J1.S2 (SHIELD), J3.1, J8.1, J9.S1 (Shield), J9.S2 (Shield), J11.1, J12.S1 (Shield), J12.S2 (Shield), R27.2, R29.2, SW1.1, U1.8 (GND), U1.10 (TEST), U1.15 (SSCK), U1.17 (PAD), U2.20 (TESTMODE), U2.42 (BOOT0), U2.44 (GND), U2.49 (EPAD), U3.5 (GND); also elsewhere on the board
I2C_SCL: NT5.1, U2.40 (PB6)
I2C_SDA: NT4.1, U2.41 (PB7)
SWD_CLK: J1.3, U2.38 (PA14_SWD_CLK)
SWD_IO: J1.2, U2.37 (PA13_SWD_IO)
USART_TX: J1.1, U2.13 (PA2), U3.4 (D)
VBUS: C3.1, C8.1, C9.1, D2.1, J2.1, J7.1, R26.1, U2.6 (VREG12), U2.8 (VM); also elsewhere on the board

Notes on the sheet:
RS485 Transceiver
PF0 and PF1 do not have ADCs or Timers
Short VREG12 to VBUS if VM<15
Up to 600mA gate drive
DC/DC Switching 320mA peak
Integrated MCU and 3-phase gate driver
TVS clamp to 23V
with the 100mA comparator setting 121k limits transient current to 60A.
Don't need diodes because if VBUS>15 or VBUS<0 then we got other problems
Magnetic angle sensor
Communication connectors
SWD Connector Must apply VBUS when using SWD
for powering externals
Status LEDs RED on when high-Z or HIGH GREEN on when LOW
